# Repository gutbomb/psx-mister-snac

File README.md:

# psx-mister-snac

This is based on schematics published here: https://github.com/blue212/SNAC-PSX

the screw holes in the case model are designed to use m2.5 screws and m2.5x4 heat set inserts.

You'll need a controller input unit from a real playstation.  it is designed to use the original ribbon cable.

Enjoy!

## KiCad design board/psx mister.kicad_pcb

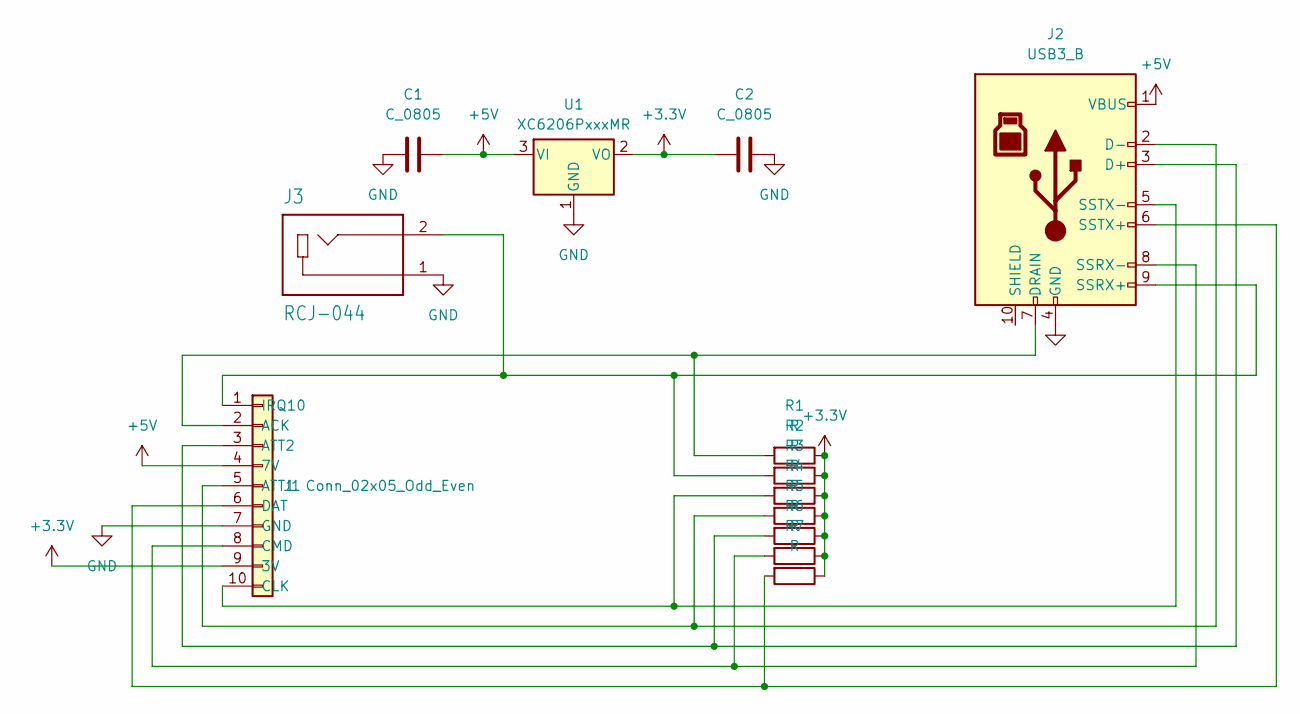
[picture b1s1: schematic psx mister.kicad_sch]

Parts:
C1, C2: C_0805; C_0805_2012Metric
J1: Conn_02x05_Odd_Even; FPC-SMD_10P-P1.00-L3.4-W13.0
J2: USB3_B; U-B-M9DD-W-1
J3: RCJ-044; CUI_RCJ-044
R1, R2, R3, R4, R5, R6, R7: R; R_0603_1608Metric
U1: XC6206PxxxMR; SOT-23-3

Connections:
+3.3V: C2.1, J1.9 (3V), R1.1, R2.1, R3.1, R4.1, R5.1, R6.1, R7.1, U1.2 (VO)
+5V: C1.2, J1.4 (7V), J2.1 (VBUS), U1.3 (VI)
GND: C1.1, C2.2, J1.7 (GND), J2.4 (GND), J3.1, U1.1 (GND)
unnamed: J1.2 (ACK), J2.7 (DRAIN), R1.2
unnamed: J1.5 (ATT1), J2.2 (D-), R4.2
unnamed: J1.3 (ATT2), J2.3 (D+), R5.2
unnamed: J1.10 (CLK), J2.5 (SSTX-), R3.2
unnamed: J1.8 (CMD), J2.8 (SSRX-), R6.2
unnamed: J1.6 (DAT), J2.6 (SSTX+), R7.2
unnamed: J1.1 (IRQ10), J2.9 (SSRX+), J3.2, R2.2

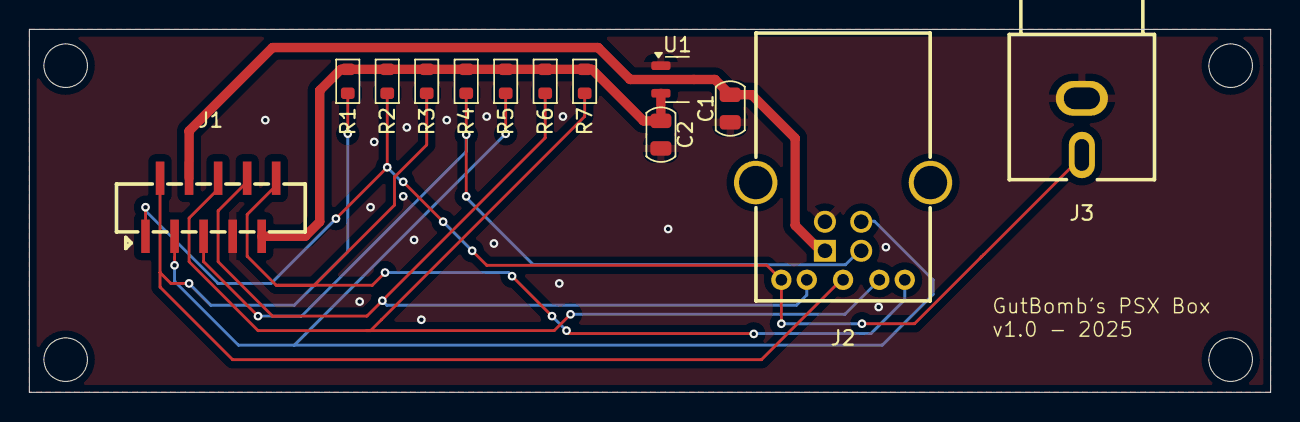
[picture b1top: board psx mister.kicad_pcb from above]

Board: 2 copper layers, 85.5 x 25.0 mm, 13 parts (0 on the bottom side), 10 nets.

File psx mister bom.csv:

Id,Designator,Footprint,Quantity,Designation,Supplier and ref,,
1,J3,CONN-TH_AV-5,1,AV-5,BOOMELE(Boom Precision Elec) AV-5,,
2,J1,FPC-SMD_10P-P1.00-L3.4-W13.0,1,AFB10-S10LCA-00,JUSHUO AFB10-S10LCA-00,,
3,U1,SOT-23-3,1,XC6206PxxxMR,Torex Semicon XC6206P332MR-G,,
4,"R1,R7,R4,R3,R5,R6,R2",R_0603_1608Metric,7,1K,YAGEO RC0603FR-071KL,,
5,"C1,C2",C_0805_2012Metric,2,1uf,Samsung Electro-Mechanics CL21B105KBFNNNE,,
6,J2,U-B-M9DD-W-1,1,U-B-M9DD-W-1,Korean Hroparts Elec U-B-M9DD-W-1,,

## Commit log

2025-07-21 public release
2025-07-21 remove .DS_Store
2025-07-21 fixed error
2025-07-21 fixed error again
2025-07-23 fixed gitignore
